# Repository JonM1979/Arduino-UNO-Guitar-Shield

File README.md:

# Arduino-UNO-Guitar-Shield

** This project is based on ElectroSmash's Arduino UNO Shield, all credit and 
similarities goes to them: https://www.electrosmash.com/pedalshield-uno **

This repository documents my personal recreation of the PedalSHIELD UNO project, an open-source programmable guitar pedal based on the Arduino UNO.

**The Primary Goal of This Project Is Educational:**
I undertook this build to deepen my understanding of PCB design and hardware manufacturing workflows. By reverse-engineering and rebuilding an existing open-source project, I aimed to:

* Learn the fundamentals of schematic capture and PCB layout.
* Gain hands-on experience with EDA tools and fabrication processes.
* Understand the practical challenges of bringing a hardware design from concept to physical board.
* Explore embedded audio processing using Arduino.

**This Repo Includes:**
* My custom PCB design files (schematics, layout, Gerbers).
* Notes and documentation on the design and manufacturing process.
* Photos and testing results from the assembled board.
* Reflections and lessons learned throughout the project.

**Personal Modifications and Reflections:**
While the core of this project was originally developed by ElectroSmash, I wanted to extend its functionality by integrating an OLED display to show the currently loaded effect on the Arduino. This small addition helped me explore how to interface displays with microcontrollers and consider user experience in hardware design.

**Design Improvements:** 
One key improvement I would make in a future revision is to increase the size of the copper pads. During assembly, I found that the small pad sizes made soldering more difficult—often resulting in cold joints or excessive solder use. Larger pads would improve solderability and make the process more forgiving and enjoyable. 

I'm also considering a Version 2.0 of the board that uses SMD components to reduce the overall footprint. Ideally, I’d like to integrate the OLED display directly onto the PCB for a more compact and professional design.

**What I Learned:**
This project was a deep dive into the end-to-end PCB design workflow. I spent a significant amount of time learning how to:

* Use KiCad 9 for schematic capture and PCB layout.
* Create custom symbols and footprints for components not found in the standard libraries.
* Select appropriate footprints (and learn the difference between THT and SMD).
* Troubleshoot issues like obsolete parts, incorrect footprints, and soldering challenges.

I encountered many real-world problems—such as not finding a footprint for a 3PDT switch and having to create one from scratch, or dealing with solder bridges and cold joints during assembly. These challenges taught me how to problem-solve independently, research effectively, and persist through trial and error.

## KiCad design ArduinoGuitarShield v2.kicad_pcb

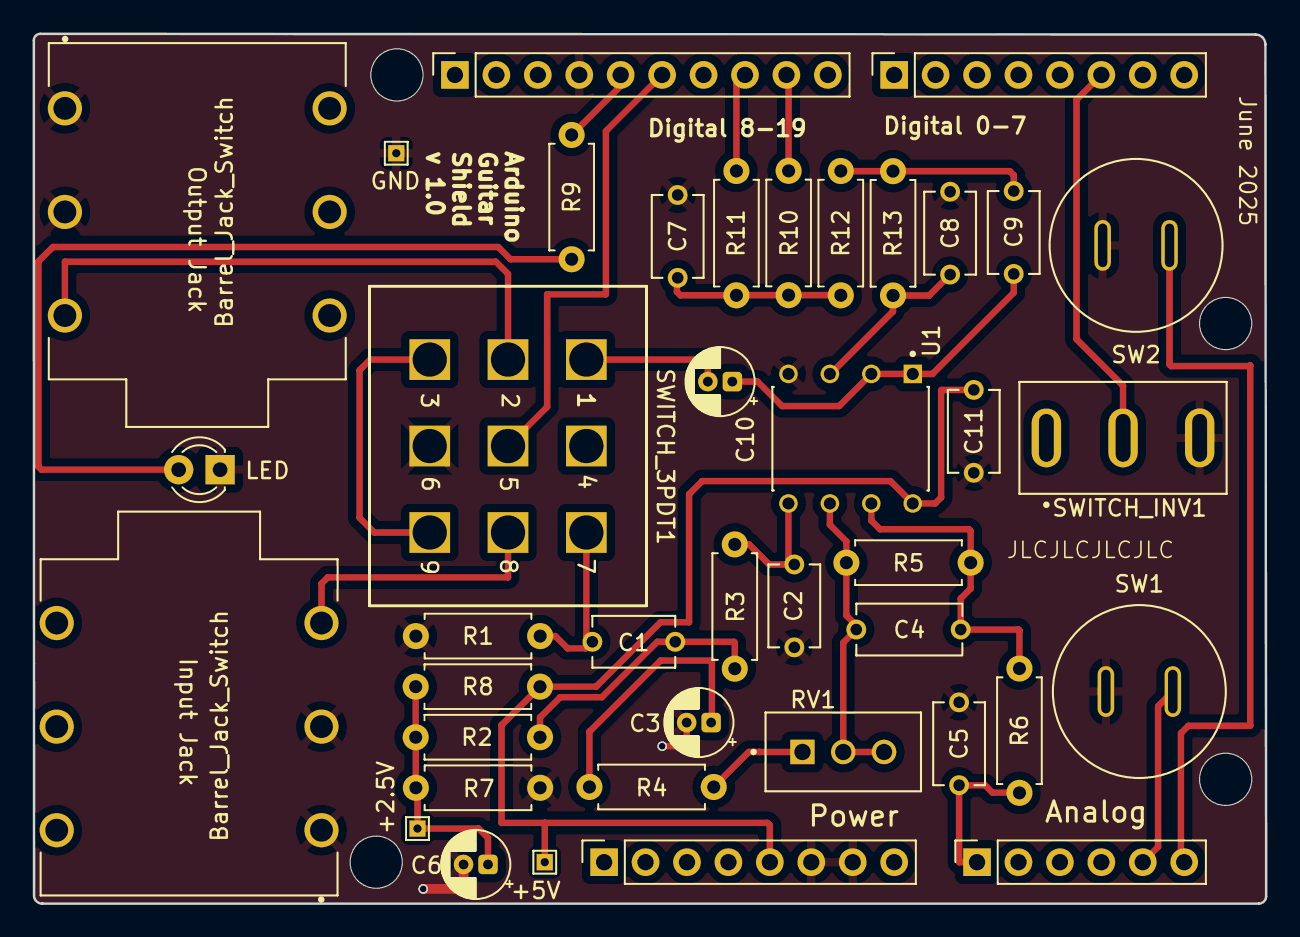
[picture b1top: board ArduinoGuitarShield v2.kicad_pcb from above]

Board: 2 copper layers, 75.5 x 53.3 mm, 44 parts (0 on the bottom side), 27 nets.

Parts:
+2.5V: 2V5; TestPoint_THTPad_1.0x1.0mm_Drill0.5mm
+5V: 5V TP; TestPoint_THTPad_1.0x1.0mm_Drill0.5mm
Barrel_Jack_Switch: Barrel_Jack_Switch; NEUTRIK_NMJ6HCD2
Barrel_Jack_Switch#2: Barrel_Jack_Switch; NEUTRIK_NMJ6HCD2
C1: 0.1u; CAPRR508W50L508T317H508
C2, C5, C7, C8, C9: 6.8n; CAPRR508W50L508T317H508
C3, C6, C10: 4.7u; CP_Radial_D4.0mm_P1.50mm
C4: 270p; D271K20Y5PH63L6R
C11: 100n; CAPRR508W50L508T317H508
GND: GND TP; TestPoint_THTPad_1.0x1.0mm_Drill0.5mm
J1: Power; PinSocket_1x08_P2.54mm_Vertical
J2: Digital/PWM; PinSocket_1x10_P2.54mm_Vertical
J3: Analog; PinSocket_1x06_P2.54mm_Vertical
J4: Digital/PWM; PinSocket_1x08_P2.54mm_Vertical
LED: LED; LED_D3.0mm
MH1, MH2, MH3, MH4: MountingHole_3.2mm
R1, R2: 1M; R_Axial_DIN0207_L6.3mm_D2.5mm_P7.62mm_Horizontal
R3, R4, R6, R9, R10, R12, R13: 4.7K; R_Axial_DIN0207_L6.3mm_D2.5mm_P7.62mm_Horizontal
R5, R7, R8: 100K; R_Axial_DIN0207_L6.3mm_D2.5mm_P7.62mm_Horizontal
R11: 1.2M; R_Axial_DIN0207_L6.3mm_D2.5mm_P7.62mm_Horizontal
RV1: 500K; TRIM_PV36W504C01B00
SW1, SW2: SW_Push; SW_103-1013-EVX
SWITCH_3PDT1: SF17020F-0302-21R-L-015
SWITCH_INV1: SW_100SP1T1B1M1QEH
U1: TL972IP; 595-TL972IP

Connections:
+5V: +5V.1, C11.2, J1.5, R8.1, U1.8
/2: J4.6, SWITCH_INV1.2
/12: J2.6, SWITCH_3PDT1.5
/13: J2.5, R9.1
/*9: J2.9, R10.1
/*10: J2.8, R11.1
/+2V5: +2.5V.1, C6.1, R2.2, R7.1, R8.2
/A0: C5.1, J3.1, R6.2
/A4: J3.5, SW1.2
/A5: J3.6, SW2.2
/Bypass: SWITCH_3PDT1.3, SWITCH_3PDT1.9
/FX Out: C10.2, SWITCH_3PDT1.1
/FX_IN: C1.1, R1.1, SWITCH_3PDT1.7
/Input Jack: Barrel_Jack_Switch#2.1, SWITCH_3PDT1.8
/Output Jack: Barrel_Jack_Switch.1, SWITCH_3PDT1.2
GND: Barrel_Jack_Switch.2, Barrel_Jack_Switch.3, Barrel_Jack_Switch#2.2, Barrel_Jack_Switch#2.3, C2.2, C3.2, C5.2, C6.2, C7.2, C8.2, C11.1, GND.1, J1.6, J1.7, J2.4, LED.1 (K), R1.2, R7.2, SW1.1, SW2.1, SWITCH_3PDT1.6, SWITCH_INV1.3, U1.4
unnamed: C1.2, R2.1, R3.1
unnamed: C2.1, R3.2, U1.5
unnamed: C3.1, R4.1
unnamed: C4.1, R5.1, RV1.2, RV1.3, U1.6
unnamed: C4.2, R5.2, R6.1, U1.7
unnamed: C7.1, R10.2, R11.2, R12.1
unnamed: C8.1, R13.2, U1.3
unnamed: C9.1, R12.2, R13.1
unnamed: C9.2, C10.1, U1.1, U1.2
unnamed: LED.2 (A), R9.2
unnamed: R4.2, RV1.1

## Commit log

2025-06-30 Add files via upload
    These are the Gerber files used to manufacture the PCB. I personally used JLCPCB to order my PCB so I am not sure if other PCB manufacturers require different files or not. If you have any questions 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
2025-06-30 README.md
2025-07-03 shield_distortion.ino
2025-07-03 shield_fuzz.ino
2025-07-03 shield_clean.ino
2025-07-03 shield_delay.ino
2025-07-03 shield_signal_generator.ino
2025-08-04 Create assets
